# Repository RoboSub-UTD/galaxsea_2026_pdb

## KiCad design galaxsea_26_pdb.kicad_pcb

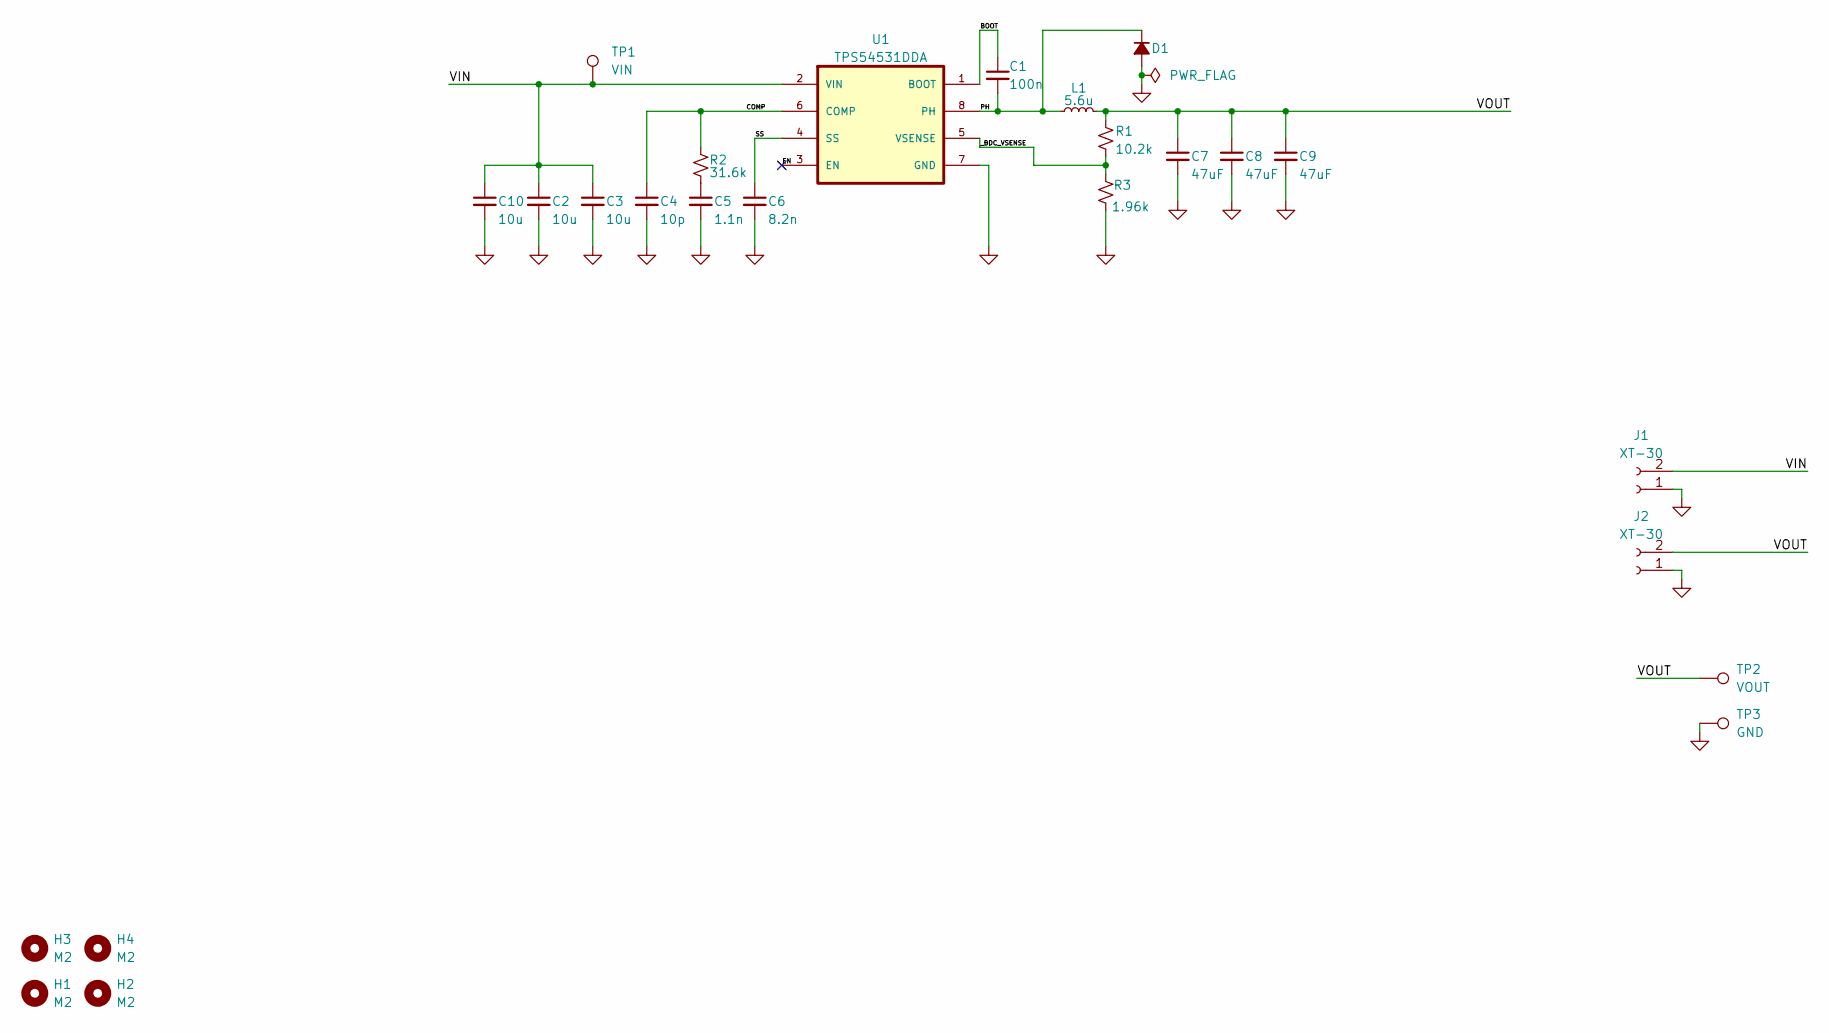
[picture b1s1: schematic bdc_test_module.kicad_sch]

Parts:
C1: 100n; C_0805_2012Metric
C2, C3, C10: 10u; C_0805_2012Metric
C4: 10p; C_0805_2012Metric
C5: 1.1n; C_0805_2012Metric
C6: 8.2n; C_0805_2012Metric
C7, C8, C9: 47uF; C_0805_2012Metric
D1: CHANGE FOOTPRINT LATER; D_SMC
H1, H2, H3, H4: M2; MountingHole_2.2mm_M2
J1, J2: XT-30; AMASS_XT30UPB-F_1x02_P5.0mm_Vertical
L1: 5.6u; L_Vishay_IHLP-2525
R1: 10.2k; R_0805_2012Metric
R2: 31.6k; R_0805_2012Metric
R3: 1.96k; R_0805_2012Metric
TP1: VIN; TestPoint_Keystone_5005-5009_Compact
TP2: VOUT; TestPoint_Keystone_5005-5009_Compact
TP3: GND; TestPoint_Keystone_5005-5009_Compact
U1: TPS54531DDA; VREG_LM5017MR_NOPB

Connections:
/BDC Test Module/BOOT: C1.1, U1.1 (BOOT)
/BDC Test Module/COMP: C4.1, R2.2, U1.6 (COMP)
/BDC Test Module/EN: U1.3 (EN)
/BDC Test Module/PH: C1.2, D1.1 (K), L1.1, U1.8 (PH)
/BDC Test Module/SS: C6.1, U1.4 (SS)
/BDC Test Module/VIN: C2.1, C3.1, C10.1, J1.2, TP1.1, U1.2 (VIN)
/BDC Test Module/VOUT: C7.1, C8.1, C9.1, J2.2, L1.2, R1.1, TP2.1
/BDC Test Module/_BDC_VSENSE: R1.2, R3.1, U1.5 (VSENSE)
GND: C2.2, C3.2, C4.2, C5.2, C6.2, C7.2, C8.2, C9.2, C10.2, D1.2 (A), J1.1, J2.1, R3.2, TP3.1, U1.7 (GND)
unnamed: C5.1, R2.1

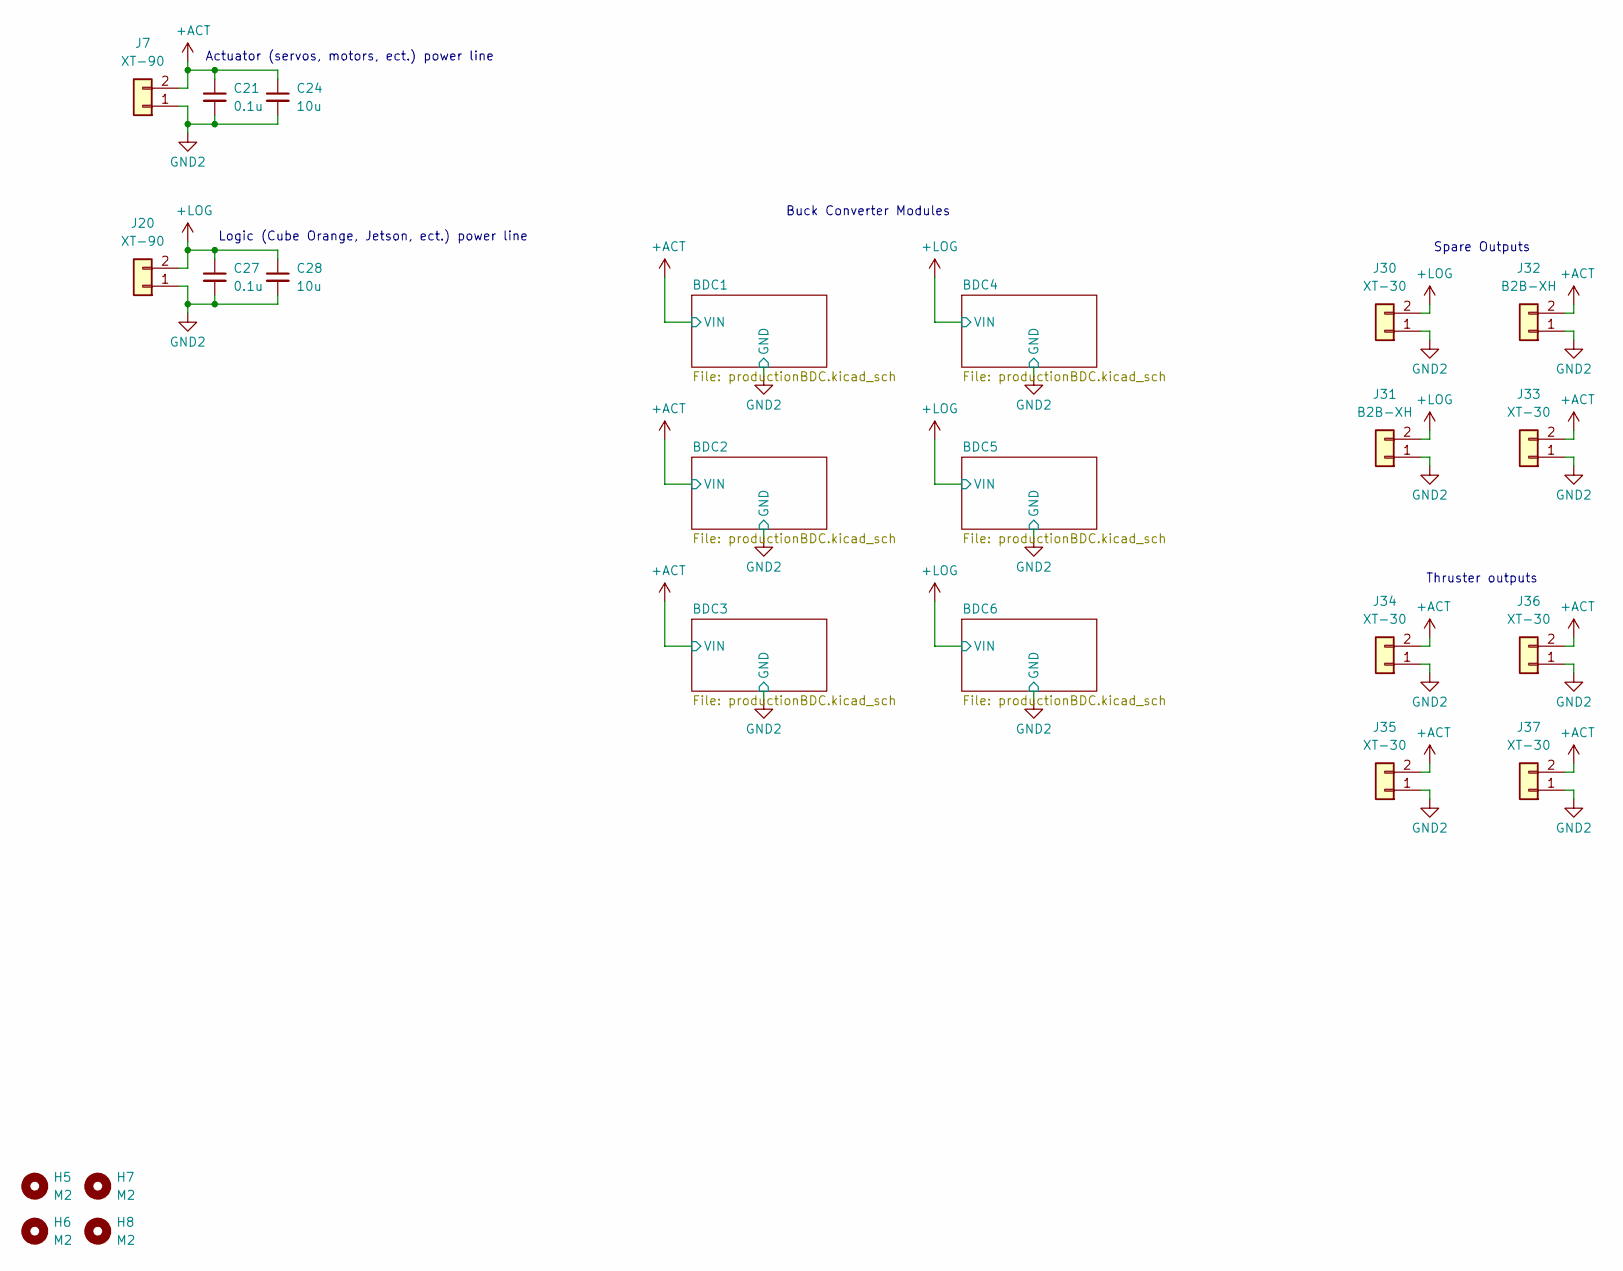
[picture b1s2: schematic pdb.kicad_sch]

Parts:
C21, C27: 0.1u; C_0805_2012Metric
C24, C28: 10u; C_0805_2012Metric
H5, H6, H7, H8: M2; MountingHole_2.2mm_M2
J7, J20: XT-90; XT90_V
J30, J33, J34, J35, J36, J37: XT-30; AMASS_XT30UPB-F_1x02_P5.0mm_Vertical
J31, J32: B2B-XH; CONN_B2B-XH-ALFSN_JST

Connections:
+ACT: C21.1, C24.1, J7.2, J32.2, J33.2, J34.2, J35.2, J36.2, J37.2; also elsewhere on the board
+LOG: C27.1, C28.1, J20.2, J30.2, J31.2; also elsewhere on the board
GND2: C21.2, C24.2, C27.2, C28.2, J7.1, J20.1, J30.1, J31.1, J32.1, J33.1, J34.1, J35.1, J36.1, J37.1; also elsewhere on the board

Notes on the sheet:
Actuator (servos, motors, ect.) power line
Logic (Cube Orange, Jetson, ect.) power line
Thruster outputs
Spare Outputs
Buck Converter Modules

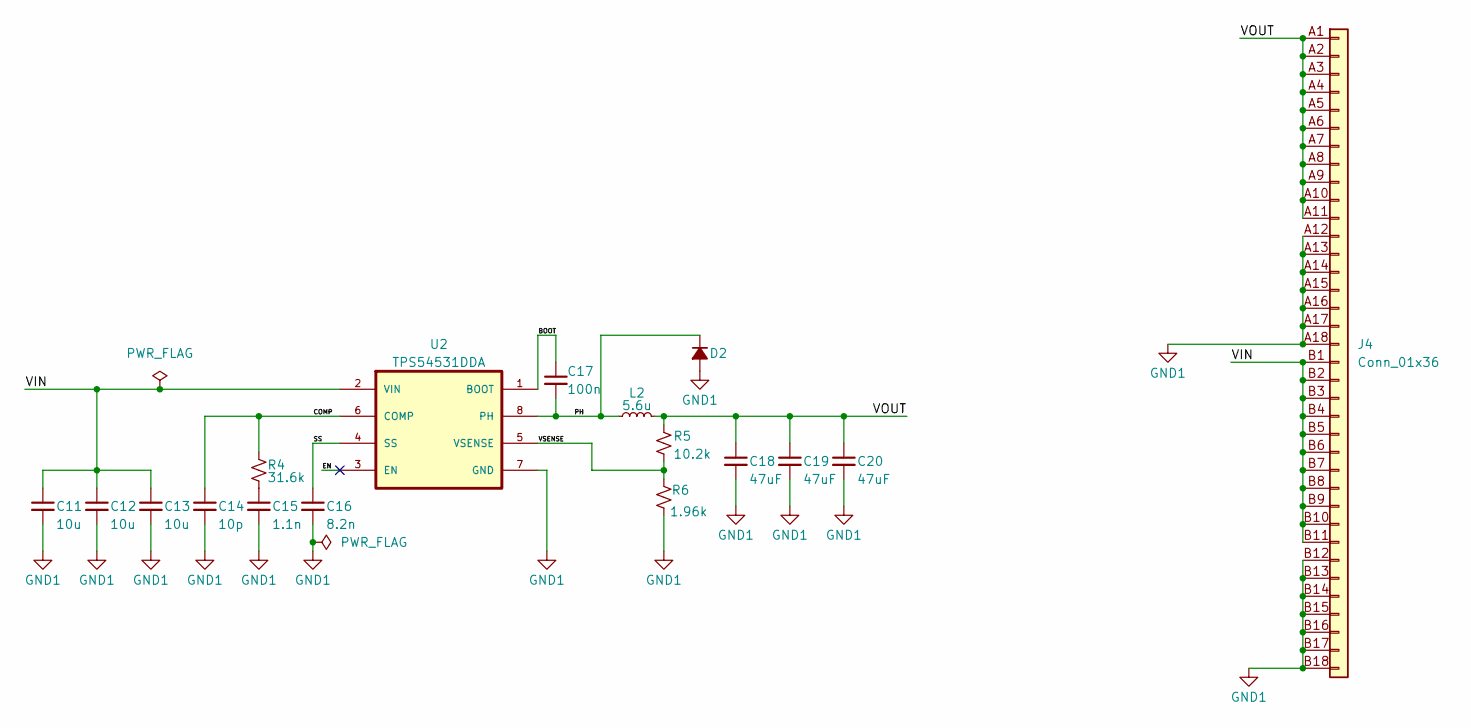
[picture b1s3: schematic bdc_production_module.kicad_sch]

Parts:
C11, C12, C13: 10u; C_0805_2012Metric
C14: 10p; C_0805_2012Metric
C15: 1.1n; C_0805_2012Metric
C16: 8.2n; C_0805_2012Metric
C17: 100n; C_0805_2012Metric
C18, C19, C20: 47uF; C_0805_2012Metric
D2: CHANGE FOOTPRINT LATER; D_SMC
J4: Conn_01x36; BUS_PCIexpress_x1
L2: 5.6u; L_Vishay_IHLP-2525
R4: 31.6k; R_0805_2012Metric
R5: 10.2k; R_0805_2012Metric
R6: 1.96k; R_0805_2012Metric
U2: TPS54531DDA; VREG_LM5017MR_NOPB

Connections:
/BDC Production Module/BOOT: C17.1, U2.1 (BOOT)
/BDC Production Module/COMP: C14.1, R4.2, U2.6 (COMP)
/BDC Production Module/EN: U2.3 (EN)
/BDC Production Module/PH: C17.2, D2.1 (K), L2.1, U2.8 (PH)
/BDC Production Module/SS: C16.1, U2.4 (SS)
/BDC Production Module/VIN: C11.1, C12.1, C13.1, J4.B1 (Pin_19), J4.B2 (Pin_20), J4.B3 (Pin_21), J4.B4 (Pin_22), J4.B5 (Pin_23), J4.B6 (Pin_24), J4.B7 (Pin_25), J4.B8 (Pin_26), J4.B9 (Pin_27), J4.B10 (Pin_28), J4.B11 (Pin_29), U2.2 (VIN)
/BDC Production Module/VOUT: C18.1, C19.1, C20.1, J4.A1 (Pin_1), J4.A2 (Pin_2), J4.A3 (Pin_3), J4.A4 (Pin_4), J4.A5 (Pin_5), J4.A6 (Pin_6), J4.A7 (Pin_7), J4.A8 (Pin_8), J4.A9 (Pin_9), J4.A10 (Pin_10), J4.A11 (Pin_11), L2.2, R5.1
/BDC Production Module/VSENSE: R5.2, R6.1, U2.5 (VSENSE)
GND1: C11.2, C12.2, C13.2, C14.2, C15.2, C16.2, C18.2, C19.2, C20.2, D2.2 (A), J4.A12 (Pin_12), J4.A13 (Pin_13), J4.A14 (Pin_14), J4.A15, J4.A16 (Pin_16), J4.A17 (Pin_17), J4.A18 (Pin_18), J4.B12 (Pin_30), J4.B13 (Pin_31), J4.B14 (Pin_32), J4.B15 (Pin_33), J4.B16 (Pin_34), J4.B17 (Pin_35), J4.B18 (Pin_36), R6.2, U2.7 (GND)
unnamed: C15.1, R4.1

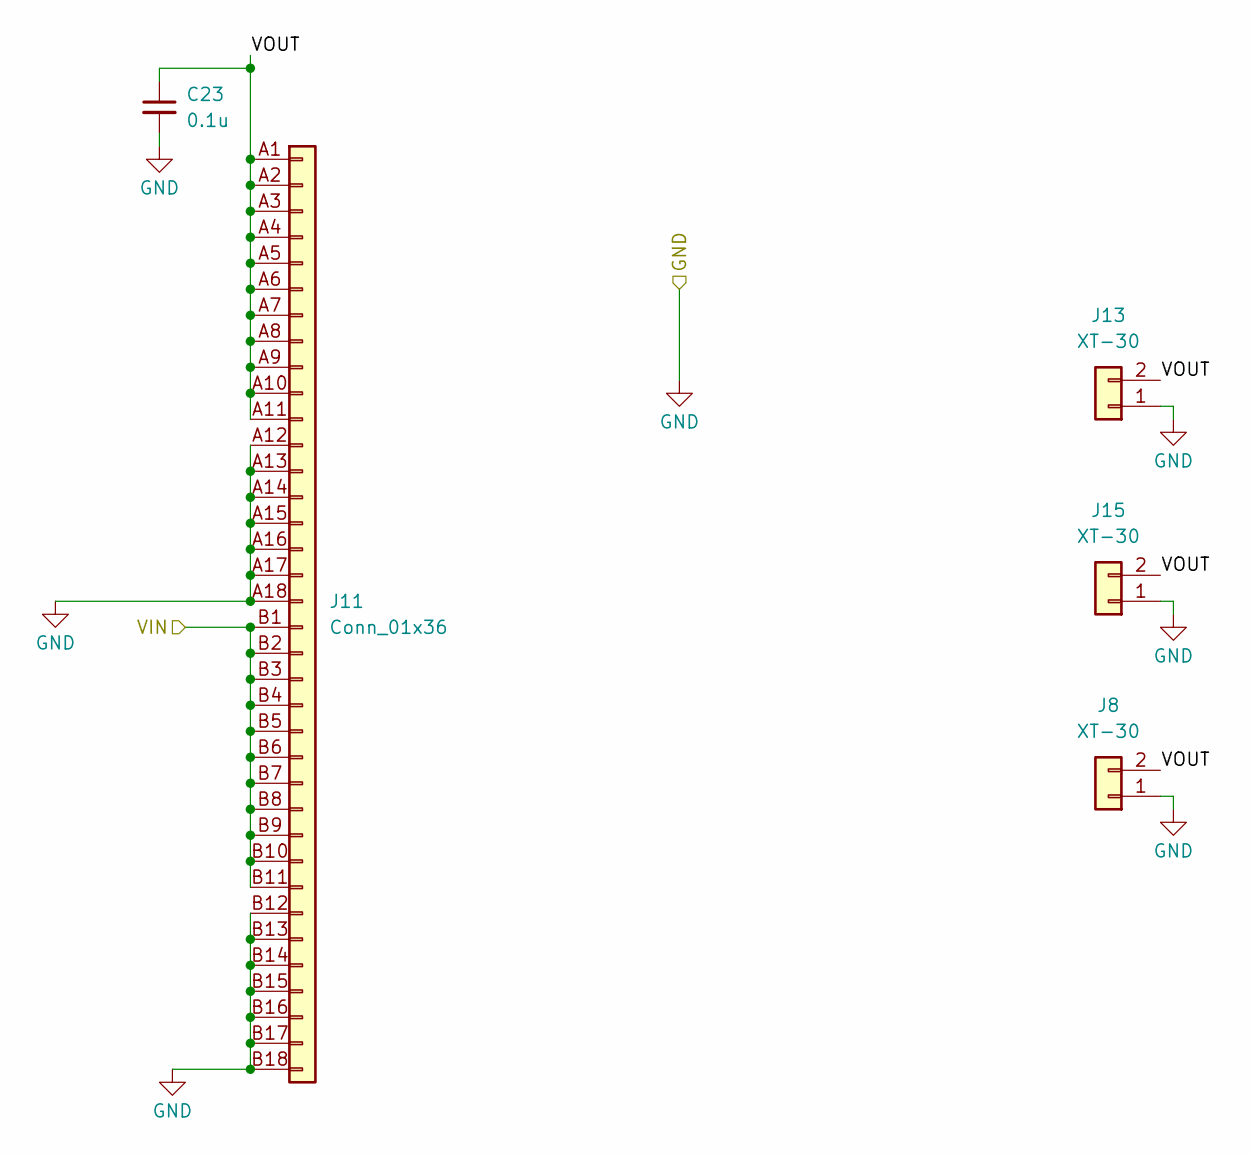
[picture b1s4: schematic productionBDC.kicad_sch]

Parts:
C23: 0.1u; C_0805_2012Metric
J8, J13, J15: XT-30; AMASS_XT30UPB-F_1x02_P5.0mm_Vertical
J11: Conn_01x36; CONN_10018784_AMP

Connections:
+ACT: J11.B1 (Pin_19), J11.B2 (Pin_20), J11.B3 (Pin_21), J11.B4 (Pin_22), J11.B5 (Pin_23), J11.B6 (Pin_24), J11.B7 (Pin_25), J11.B8 (Pin_26), J11.B9 (Pin_27), J11.B10 (Pin_28), J11.B11 (Pin_29); also elsewhere on the board
/PDB/BDC1/VOUT: C23.1, J8.2, J11.A1 (Pin_1), J11.A2 (Pin_2), J11.A3 (Pin_3), J11.A4 (Pin_4), J11.A5 (Pin_5), J11.A6 (Pin_6), J11.A7 (Pin_7), J11.A8 (Pin_8), J11.A9 (Pin_9), J11.A10 (Pin_10), J11.A11 (Pin_11), J13.2, J15.2
GND2: C23.2, J8.1, J11.A12 (Pin_12), J11.A13 (Pin_13), J11.A14 (Pin_14), J11.A15, J11.A16 (Pin_16), J11.A17 (Pin_17), J11.A18 (Pin_18), J11.B12 (Pin_30), J11.B13 (Pin_31), J11.B14 (Pin_32), J11.B15 (Pin_33), J11.B16 (Pin_34), J11.B17 (Pin_35), J11.B18 (Pin_36), J13.1, J15.1; also elsewhere on the board

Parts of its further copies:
C22, C25, C26, C29, C30: 0.1u; C_0805_2012Metric
J3, J5, J19, J21, J26: Conn_01x36; CONN_10018784_AMP
J6, J9, J10, J12, J14, J16, J17, J18, J22, J23, J24, J25, J27, J28, J29: XT-30; AMASS_XT30UPB-F_1x02_P5.0mm_Vertical

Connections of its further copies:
+ACT: J3.B1 (Pin_19), J3.B2 (Pin_20), J3.B3 (Pin_21), J3.B4 (Pin_22), J3.B5 (Pin_23), J3.B6 (Pin_24), J3.B7 (Pin_25), J3.B8 (Pin_26), J3.B9 (Pin_27), J3.B10 (Pin_28), J3.B11 (Pin_29), J19.B1 (Pin_19), J19.B2 (Pin_20), J19.B3 (Pin_21), J19.B4 (Pin_22), J19.B5 (Pin_23), J19.B6 (Pin_24), J19.B7 (Pin_25), J19.B8 (Pin_26), J19.B9 (Pin_27), J19.B10 (Pin_28), J19.B11 (Pin_29); also elsewhere on the board
+LOG: J5.B1 (Pin_19), J5.B2 (Pin_20), J5.B3 (Pin_21), J5.B4 (Pin_22), J5.B5 (Pin_23), J5.B6 (Pin_24), J5.B7 (Pin_25), J5.B8 (Pin_26), J5.B9 (Pin_27), J5.B10 (Pin_28), J5.B11 (Pin_29), J21.B1 (Pin_19), J21.B2 (Pin_20), J21.B3 (Pin_21), J21.B4 (Pin_22), J21.B5 (Pin_23), J21.B6 (Pin_24), J21.B7 (Pin_25), J21.B8 (Pin_26), J21.B9 (Pin_27), J21.B10 (Pin_28), J21.B11 (Pin_29), J26.B1 (Pin_19), J26.B2 (Pin_20), J26.B3 (Pin_21), J26.B4 (Pin_22), J26.B5 (Pin_23), J26.B6 (Pin_24), J26.B7 (Pin_25), J26.B8 (Pin_26), J26.B9 (Pin_27), J26.B10 (Pin_28), J26.B11 (Pin_29); also elsewhere on the board
/PDB/BDC2/VOUT: C22.1, J3.A1 (Pin_1), J3.A2 (Pin_2), J3.A3 (Pin_3), J3.A4 (Pin_4), J3.A5 (Pin_5), J3.A6 (Pin_6), J3.A7 (Pin_7), J3.A8 (Pin_8), J3.A9 (Pin_9), J3.A10 (Pin_10), J3.A11 (Pin_11), J9.2, J14.2, J17.2
/PDB/BDC3/VOUT: C25.1, J10.2, J16.2, J19.A1 (Pin_1), J19.A2 (Pin_2), J19.A3 (Pin_3), J19.A4 (Pin_4), J19.A5 (Pin_5), J19.A6 (Pin_6), J19.A7 (Pin_7), J19.A8 (Pin_8), J19.A9 (Pin_9), J19.A10 (Pin_10), J19.A11 (Pin_11), J23.2
/PDB/BDC4/VOUT: C26.1, J5.A1 (Pin_1), J5.A2 (Pin_2), J5.A3 (Pin_3), J5.A4 (Pin_4), J5.A5 (Pin_5), J5.A6 (Pin_6), J5.A7 (Pin_7), J5.A8 (Pin_8), J5.A9 (Pin_9), J5.A10 (Pin_10), J5.A11 (Pin_11), J6.2, J12.2, J18.2
/PDB/BDC5/VOUT: C29.1, J21.A1 (Pin_1), J21.A2 (Pin_2), J21.A3 (Pin_3), J21.A4 (Pin_4), J21.A5 (Pin_5), J21.A6 (Pin_6), J21.A7 (Pin_7), J21.A8 (Pin_8), J21.A9 (Pin_9), J21.A10 (Pin_10), J21.A11 (Pin_11), J22.2, J24.2, J25.2
/PDB/BDC6/VOUT: C30.1, J26.A1 (Pin_1), J26.A2 (Pin_2), J26.A3 (Pin_3), J26.A4 (Pin_4), J26.A5 (Pin_5), J26.A6 (Pin_6), J26.A7 (Pin_7), J26.A8 (Pin_8), J26.A9 (Pin_9), J26.A10 (Pin_10), J26.A11 (Pin_11), J27.2, J28.2, J29.2
GND2: C22.2, C25.2, C26.2, C29.2, C30.2, J3.A12 (Pin_12), J3.A13 (Pin_13), J3.A14 (Pin_14), J3.A15, J3.A16 (Pin_16), J3.A17 (Pin_17), J3.A18 (Pin_18), J3.B12 (Pin_30), J3.B13 (Pin_31), J3.B14 (Pin_32), J3.B15 (Pin_33), J3.B16 (Pin_34), J3.B17 (Pin_35), J3.B18 (Pin_36), J5.A12 (Pin_12), J5.A13 (Pin_13), J5.A14 (Pin_14), J5.A15, J5.A16 (Pin_16), J5.A17 (Pin_17), J5.A18 (Pin_18), J5.B12 (Pin_30), J5.B13 (Pin_31), J5.B14 (Pin_32), J5.B15 (Pin_33), J5.B16 (Pin_34), J5.B17 (Pin_35), J5.B18 (Pin_36), J6.1, J9.1, J10.1, J12.1, J14.1, J16.1, J17.1, J18.1, J19.A12 (Pin_12), J19.A13 (Pin_13), J19.A14 (Pin_14), J19.A15, J19.A16 (Pin_16), J19.A17 (Pin_17), J19.A18 (Pin_18), J19.B12 (Pin_30), J19.B13 (Pin_31), J19.B14 (Pin_32), J19.B15 (Pin_33), J19.B16 (Pin_34), J19.B17 (Pin_35), J19.B18 (Pin_36), J21.A12 (Pin_12), J21.A13 (Pin_13), J21.A14 (Pin_14), J21.A15, J21.A16 (Pin_16), J21.A17 (Pin_17), J21.A18 (Pin_18), J21.B12 (Pin_30), J21.B13 (Pin_31), J21.B14 (Pin_32), J21.B15 (Pin_33), J21.B16 (Pin_34), J21.B17 (Pin_35), J21.B18 (Pin_36), J22.1, J23.1, J24.1, J25.1, J26.A12 (Pin_12), J26.A13 (Pin_13), J26.A14 (Pin_14), J26.A15, J26.A16 (Pin_16), J26.A17 (Pin_17), J26.A18 (Pin_18), J26.B12 (Pin_30), J26.B13 (Pin_31), J26.B14 (Pin_32), J26.B15 (Pin_33), J26.B16 (Pin_34), J26.B17 (Pin_35), J26.B18 (Pin_36), J27.1, J28.1, J29.1; also elsewhere on the board

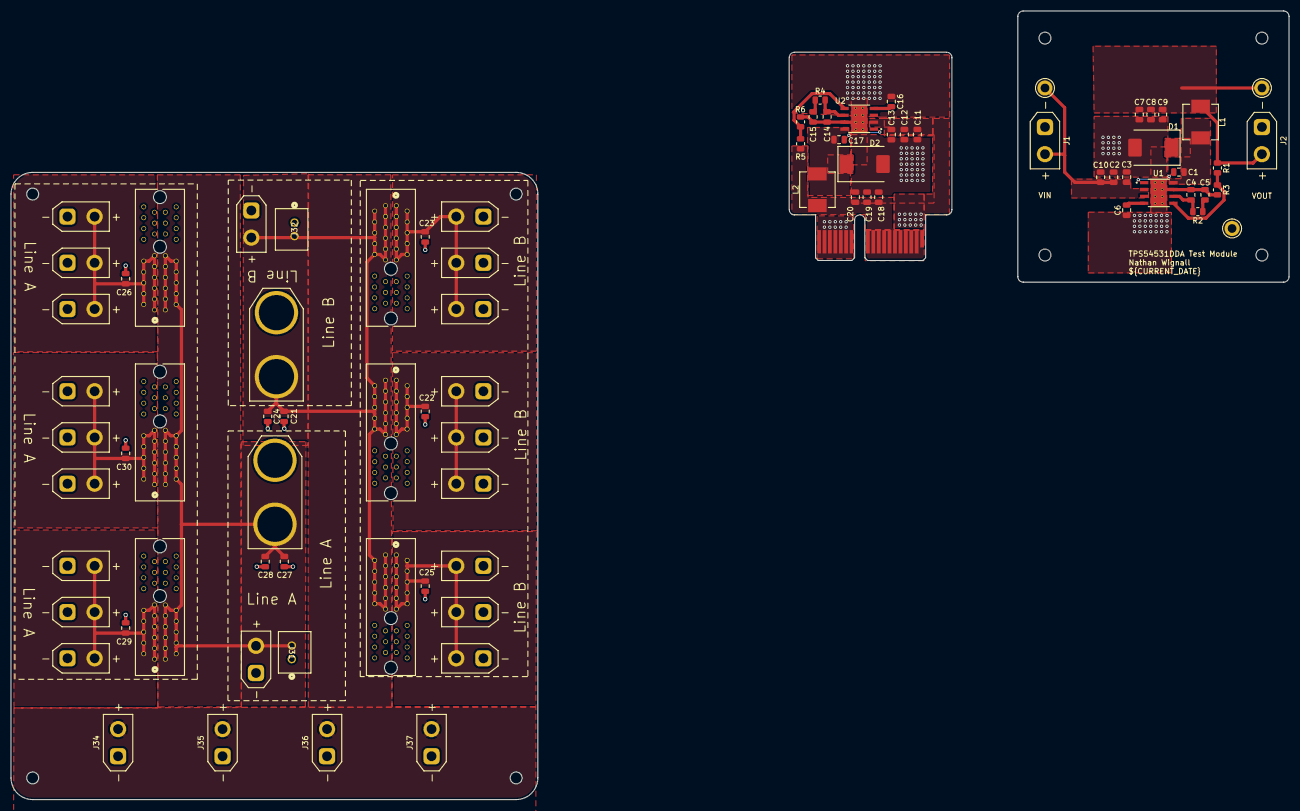
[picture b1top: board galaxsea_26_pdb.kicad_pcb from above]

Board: 2 copper layers, 235.7 x 145.4 mm, 90 parts (1 on the bottom side), 27 nets.

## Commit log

2025-06-18 Add dimensions
2025-06-18 Final pin placement
2025-06-23 Organize, make BDC Module more solderable
2025-06-23 unbreak schematic
2025-06-23 Fix annotations
2025-06-23 pretty silkscreens
2025-06-24 Add GalaxSea Logo, Board Name, Author Name, Date to silkscreen
2025-06-25 add Fuse, LEDs
2025-06-25 Round board size
2025-06-25 Dimensions
2025-06-25 Make square
2025-06-28 Ground vias
2025-06-28 standardize trace width
2025-06-28 Add XT30 connectors
2025-09-08 update mounting
2025-09-26 Finalize schematic & layout
2025-09-26 Remove Gerber files
2025-09-26 Add inductor 3D model
2025-09-30 add JLCPCB design rules
2025-10-02 move test and production modules into seperate hierarchical sheets
2025-10-03 copy prototype board layout to production
2025-10-05 initial production module layout
2025-10-06 bevel edges!
2025-11-11 Initial PDB layout
2025-11-12 Finish proof of concept PDB
2025-11-12 Add 3D Models
2025-12-01 Prepare for PDR
2026-02-20 Finalize
2026-03-24 Add JST B2B-XH connectors
2026-04-25 Update to KiCad 10
2026-04-27 Add motor connectors
2026-04-27 Update buck converter module silkscreen
2026-04-27 Switch ESC connectors to XT-30
